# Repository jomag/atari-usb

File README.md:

Atari USB
=========

This repo contains the PCB and firmware of an Atari joystick to USB
adapter, allowing old, golden joysticks such as TAC-2 to be used with
modern computers, or products such as "The C64" that use USB for
joysticks.

**"The C64" is picky about joysticks, and this firmware has not yet
been confirmed to be compatible with it. This will be updated.**

Architecture
------------

The adapter is primarily built around an ATmega32u4 with an Arduino
bootloader. This allows the firmware to be tweaked and flashed using
the standard Arduino IDE. Board type: "Adafruit Feather 32u4".

PCB revisions
-------------

### Rev 0

Current revision.

Everything works, but the initial bootloader transfer is a bit
complicated as it requires temporary soldering an ISP header to
a few pads on the board. This will be revisited for rev 1.

Firmware
--------

Current firmware is very simplistic, but it works well. The joystick
HID code was copied from Matthew Heironimus.

License
-------

The current release contains code from Matthew Heironimus under
the LGPL license, so the entire project is LGPL for now.

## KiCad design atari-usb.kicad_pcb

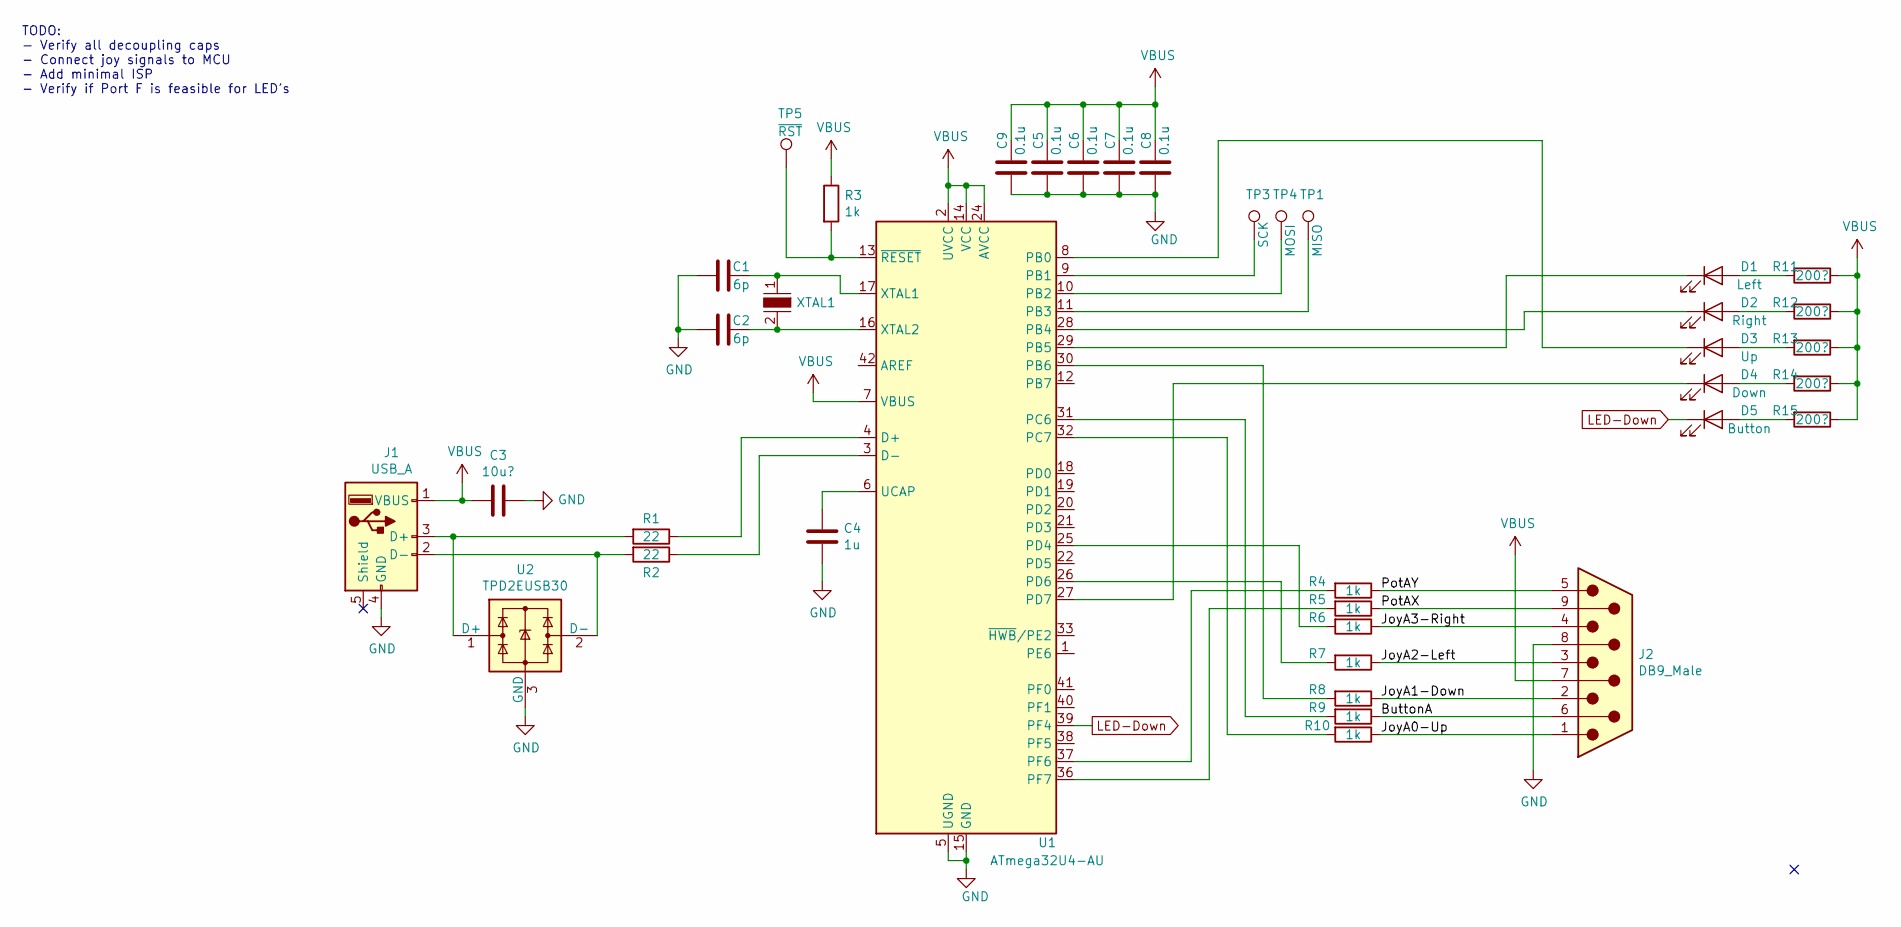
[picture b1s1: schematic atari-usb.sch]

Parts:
C1, C2: 6p; C_0603_1608Metric
C3: 10u?; C_0805_2012Metric
C4: 1u; C_0603_1608Metric
C5, C6, C7, C8, C9: 0.1u; C_0603_1608Metric
D1: Left; LED_0603_1608Metric
D2: Right; LED_0603_1608Metric
D3: Up; LED_0603_1608Metric
D4: Down; LED_0603_1608Metric
D5: Button; LED_0603_1608Metric
J1: USB_A; USB_A_CNCTech_1001-011-01101_Horizontal
J2: DB9_Male; db9-edge-hack
R1, R2: 22; R_0603_1608Metric
R3, R4, R5, R6, R7, R8, R9, R10: 1k; R_0603_1608Metric
R11, R12, R13, R14, R15: 200?; R_0603_1608Metric
TP1: MISO; TestPoint_Pad_D1.0mm
TP3: SCK; TestPoint_Pad_D1.0mm
TP4: MOSI; TestPoint_Pad_D1.0mm
TP5: ~RST; TestPoint_Pad_D1.0mm
U1: ATmega32U4-AU; TQFP-44_10x10mm_P0.8mm
U2: TPD2EUSB30; SOT-23
XTAL1: NX3225GD-8MHZ-STD-CRA-3; SMD-2_3.2x2.5mm; MPN NX3225GD-8MHZ-STD-CRA-3; Digi-Key_PN 644-1178-1-ND

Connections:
/ButtonA: J2.6, R9.1
/JoyA0-Up: J2.1, R10.1
/JoyA1-Down: J2.2, R8.1
/JoyA2-Left: J2.3, R7.1
/JoyA3-Right: J2.4, R6.1
/PotAX: J2.9, R5.1
/PotAY: J2.5, R4.1
GND: C1.2, C2.2, C3.1, C4.1, C5.1, C6.1, C7.1, C8.1, C9.1, J1.4 (GND), J2.8, U1.5 (UGND), U1.15 (GND), U1.23 (GND), U1.35 (GND), U1.43 (GND), U2.3 (GND)
LED-Down: D5.1 (K), U1.39 (PF4)
unnamed: C1.1, U1.17 (XTAL1), XTAL1.1
unnamed: C2.1, U1.16 (XTAL2), XTAL1.2
unnamed: C4.2, U1.6 (UCAP)
unnamed: D1.1 (K), U1.29 (PB5)
unnamed: D1.2 (A), R11.2
unnamed: D2.1 (K), U1.28 (PB4)
unnamed: D2.2 (A), R12.2
unnamed: D3.1 (K), U1.8 (PB0)
unnamed: D3.2 (A), R13.2
unnamed: D4.1 (K), U1.27 (PD7)
unnamed: D4.2 (A), R14.2
unnamed: D5.2 (A), R15.2
unnamed: J1.2 (D-), R2.2, U2.2 (D-)
unnamed: J1.3 (D+), R1.2, U2.1 (D+)
unnamed: R1.1, U1.4 (D+)
unnamed: R2.1, U1.3 (D-)
unnamed: R3.2, TP5.1, U1.13 (~RESET)
unnamed: R4.2, U1.37 (PF6)
unnamed: R5.2, U1.36 (PF7)
unnamed: R6.2, U1.25 (PD4)
unnamed: R7.2, U1.26 (PD6)
unnamed: R8.2, U1.30 (PB6)
unnamed: R9.2, U1.31 (PC6)
unnamed: R10.2, U1.32 (PC7)
unnamed: TP1.1, U1.11 (PB3)
unnamed: TP3.1, U1.9 (PB1)
unnamed: TP4.1, U1.10 (PB2)
VBUS: C3.2, C5.2, C6.2, C7.2, C8.2, C9.2, J1.1 (VBUS), J2.7, R3.1, R11.1, R12.1, R13.1, R14.1, R15.1, U1.2 (UVCC), U1.7 (VBUS), U1.14 (VCC), U1.24 (AVCC), U1.34 (VCC), U1.44 (AVCC)

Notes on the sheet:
TODO: - Verify all decoupling caps - Connect joy signals to MCU - Add minimal ISP - Verify if Port F is feasible for LED's

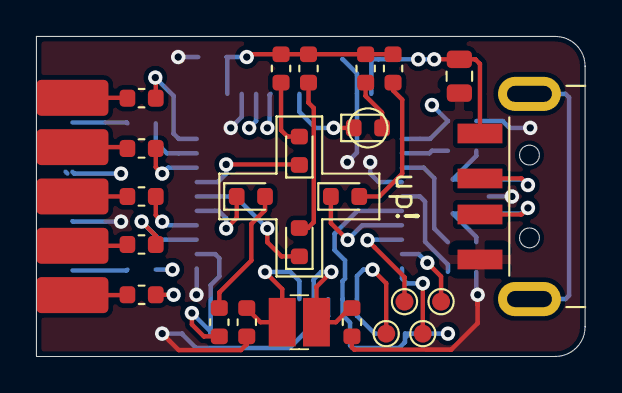
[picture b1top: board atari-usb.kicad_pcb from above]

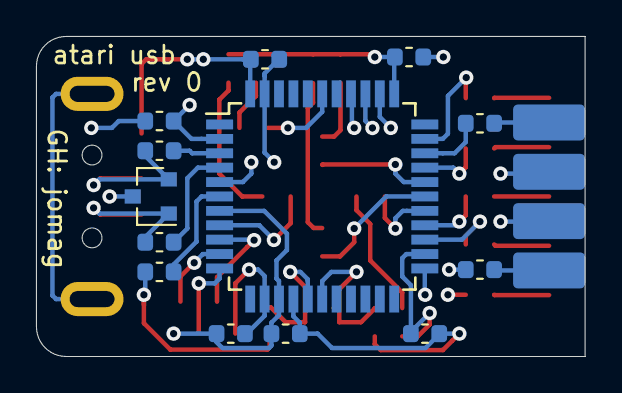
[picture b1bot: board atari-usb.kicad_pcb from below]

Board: 4 copper layers, 30.5 x 17.8 mm, 38 parts (13 on the bottom side), 37 nets.

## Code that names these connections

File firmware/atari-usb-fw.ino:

// Joystick pins:
//
// - Left: PD4 (pin 25)
// - Right: PD6 (pin 26, arduino 12)
// - Up: PC7 (pin 32, arduino 13)
// - Down: PB6 (pin 30, arduino 10)
// - Button: PC6 (pin 31, arduino 5)
//
// LED pins:
// - Left: PB5 (pin 29)
// - Right: PB4 (pin 28, arduino 9)
// - Up: PB0 (pin 8)
// - Down: PD7 (pin 27, arduino 6)
// - Button: PF4 (pin 39, arduino 21)

#include "Joystick.h"

typedef enum {
  JOY_UP = 0,
  JOY_DOWN,
  JOY_LEFT,
  JOY_RIGHT,
  JOY_BUTTON
} InputType;

InputType input_types[5] = {
  JOY_UP,
  JOY_DOWN,
  JOY_LEFT,
  JOY_RIGHT,
  JOY_BUTTON
};

bool joy_read(InputType type)
{
  switch (type) {
  case JOY_UP: return !(PINC & (1 << 7));
  case JOY_DOWN: return !(PINB & (1 << 6));
  case JOY_LEFT: return !(PIND & (1 << 6));
  case JOY_RIGHT: return !(PIND & (1 << 4));
  case JOY_BUTTON: return !(PINC & (1 << 6));
  default: return false;
  }
}

void led_set(InputType type, bool on)
{
  if (on) {
    switch (type) {
    case JOY_UP: PORTB &= ~(1 << 0); return;
    case JOY_DOWN: PORTD &= ~(1 << 7); return;
    case JOY_LEFT: PORTB &= ~(1 << 5); return;
    case JOY_RIGHT: PORTB &= ~(1 << 4); return;
    case JOY_BUTTON: PORTF &= ~(1 << 4); return;
    }
  } else {
    switch (type) {
    case JOY_UP: PORTB |= 1 << 0; return;
    case JOY_DOWN: PORTD |= 1 << 7; return;
    case JOY_LEFT: PORTB |= 1 << 5; return;
    case JOY_RIGHT: PORTB |= 1 << 4; return;
    case JOY_BUTTON: PORTF |= 1 << 4; return;
    }
  }
}

void setup() {
  // Port B: PB6 joystick, PB0+PB4+PB5 led
  DDRB = (1 << 0) | (1 << 4) | (1 << 5);
  PORTB = (1 << 6);

  // Port C: PC6+PC7 joystick
  DDRC = 0;
  PORTC = (1 << 6) | (1 << 7);
  
  // Port D: PD4+PD6 joystick, PD7 led
  DDRD = (1 << 7);
  PORTD = (1 << 4) | (1 << 6);

  // Port F: PF4 led
  DDRF = (1 << 4);
  PORTF = 0;

  Joystick.begin();
}

void loop() {
  bool left, right, up, down, button;
  uint8_t x;
  uint8_t y;

  left = joy_read(JOY_LEFT);
  right = joy_read(JOY_RIGHT);
  up = joy_read(JOY_UP);
  down = joy_read(JOY_DOWN);
  button = joy_read(JOY_BUTTON);

  led_set(JOY_UP, up);
  led_set(JOY_DOWN, down);
  led_set(JOY_LEFT, left);
  led_set(JOY_RIGHT, right);
  led_set(JOY_BUTTON, button);
  
  if (up && !down) {
    Joystick.setYAxis(-127);
  } else if (down && !up) {
    Joystick.setYAxis(127);
  } else {
    Joystick.setYAxis(0);
  }

  if (left && !right) {
    Joystick.setXAxis(-127);
  } else if (right && !left) {
    Joystick.setXAxis(127);
  } else {
    Joystick.setXAxis(0);
  }

  Joystick.setButton(0, button);
}

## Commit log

2020-04-26 Much of the schema and layout done
2020-05-06 Revision 0 done
2020-06-22 Gerbers for rev 0
2020-06-22 First working firmware
2020-06-22 Minor fixes during assembly
2020-06-22 Move PCB to subdirectory
2020-06-22 Add README.md
2020-06-22 Add license
2020-06-22 Add product photo
2020-06-22 New image size
